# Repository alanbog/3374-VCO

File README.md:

# 3374-VCO

This repository contains a circuit designed to be a clone of the CEM 3374 VCO IC used in analog synthesizers from the early 1980s such as:

* Fender Chroma Polaris
* Oberheim Matrix 12
* Oberheim Xpander
* Akai VX600.

It is designed to operate with 12V for Vcc and -5V or -6V for Vee, which is what all of the synthesizers listed above use for supply voltages. The circuit contains two oscillator channels with triangle and sawtooth wave outputs. Triangle wave outputs have an amplitude of 1/3 Vcc, and sawtooth wave outputs have an amplitude of 2/3 Vcc. Synthesizers using the CEM 3374 that generate square/pulse waves do so with external comparator circuits. 

Channel A sync is implemented. Channel B sync is not implemented, but this feature was rarely used on the CEM 3374 (None of the synthesizers listed above use it). 

A thermistor circuit is used to provede a temperature compensated reference voltage. Typically, this voltage is used as a reference for the DAC that outputs the voltage that controls the frequency of the oscillators.

This was tested on a Chroma Polaris. It should work in all of the other synthesizers listed above, but it hasn't been tested. 

For Rev 1, the oscillator circuit was updated to fix an issue with Oberheim Synthesizers being out of tune at lower notes (although this fix hasn't yet been tested on an Oberheim synthesizer).

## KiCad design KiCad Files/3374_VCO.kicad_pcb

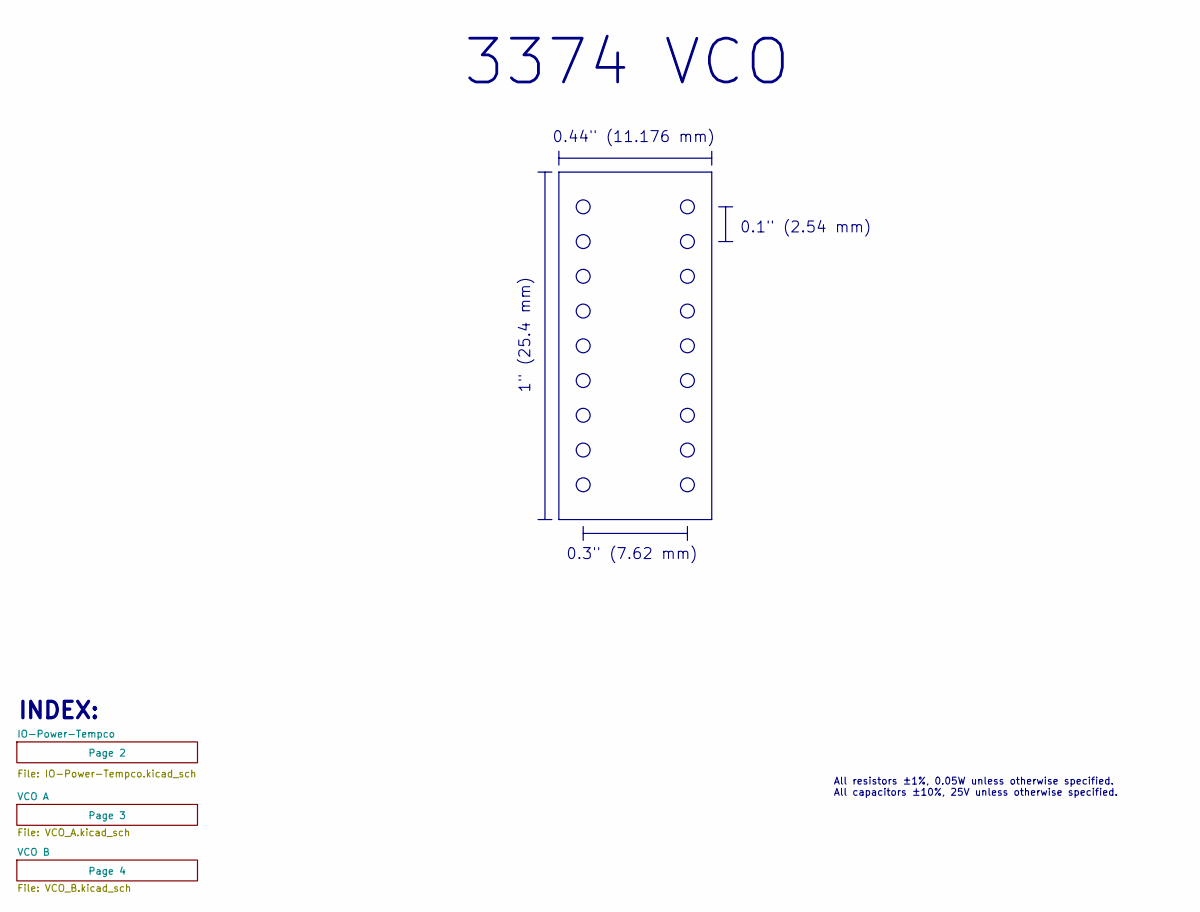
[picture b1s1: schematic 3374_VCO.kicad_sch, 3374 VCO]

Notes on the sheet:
INDEX:
0.3" (7.62 mm)
All resistors ±1%, 0.05W unless otherwise specified. All capacitors ±10%, 25V unless otherwise specified.
0.44" (11.176 mm)
3374 VCO
1" (25.4 mm)
0.1" (2.54 mm)

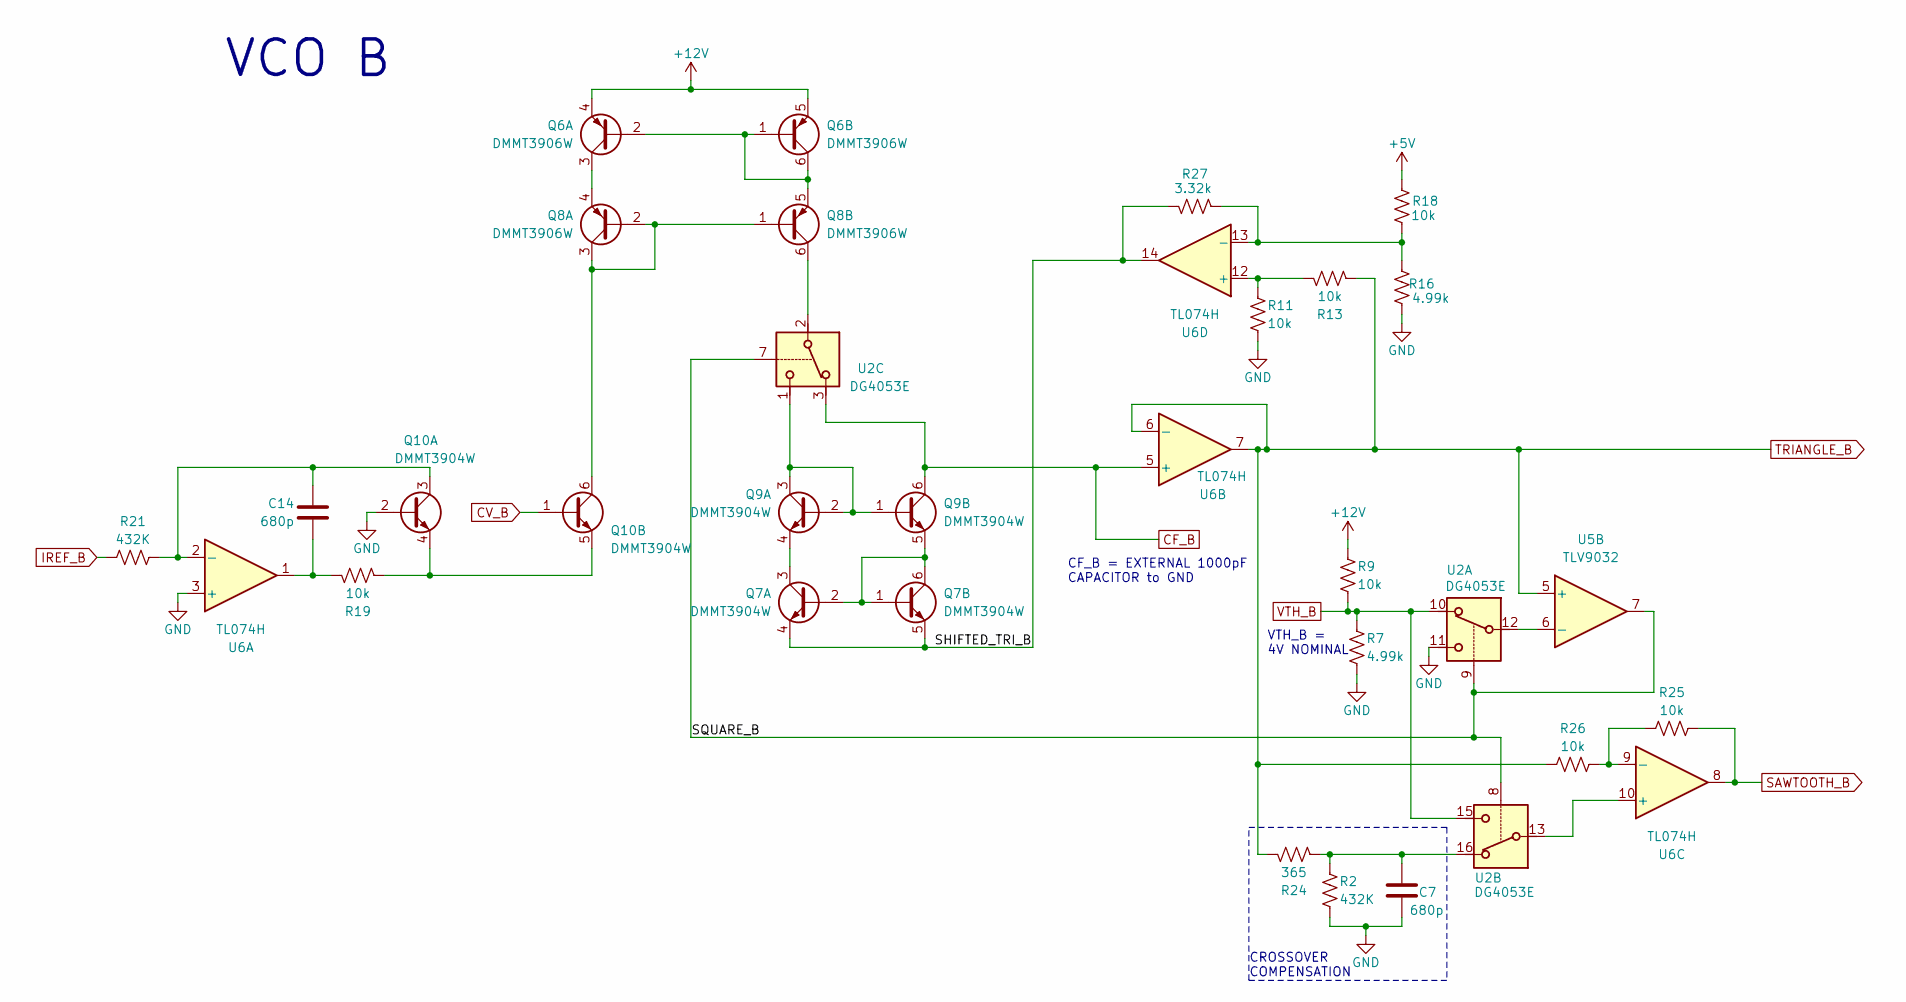
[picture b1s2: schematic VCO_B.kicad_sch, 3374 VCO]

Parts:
C7, C14: 680p; C_0201_0603Metric; Rating 25V; Tolerance 10%; Mfg PN GRM033R71E681KA01D
Q6, Q8: DMMT3906W; SOT-363_SC-70-6; Mfg PN DMMT3906W-7-F
Q7, Q9, Q10: DMMT3904W; SOT-363_SC-70-6; Mfg PN DMMT3904W-7-F
R2, R21: 432K; R_0201_0603Metric; Rating 0.05W; Tolerance 1%; Mfg PN WR02X4323FAL
R7, R16: 4.99k; R_0201_0603Metric; Rating 0.05W; Tolerance 1%; Mfg PN 0201WMF4991TEE
R9, R11, R13, R18, R19, R25, R26: 10k; R_0201_0603Metric; Rating 0.05W; Tolerance 1%; Mfg PN 0201WMF1002TEE
R24: 365; R_0201_0603Metric; Rating 0.05W; Tolerance 1%; Mfg PN 0201WMF3650TEE
R27: 3.32k; R_0201_0603Metric; Rating 0.05W; Tolerance 1%; Mfg PN 0201WMF3321TEE
U2: DG4053E; QFN_EEN-T1-GE4_VIS; Mfg PN DG4053EEN-T1-GE4
U5: TLV9032; WSON-8-1EP_2x2mm_P0.5mm_EP0.9x1.6mm; Mfg PN TLV9032DSGR
U6: TL074H; SOT23_DYY_TEX-L; Mfg PN TL074HIDYYR

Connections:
+5V: R18.2; also elsewhere on the board
+12V: Q6.4 (E1), Q6.5 (E2), R9.1; also elsewhere on the board
/VCO B/SHIFTED_TRI_B: Q7.4 (E1), Q7.5 (E2), R27.1, U6.14
/VCO B/SQUARE_B: U2.7, U2.8, U2.9, U5.7
CF_B: Q9.6 (C2), U2.3, U6.5 (+); also elsewhere on the board
CV_B: Q10.1 (B2); also elsewhere on the board
GND: C7.2, Q10.2 (B1), R2.2, R7.2, R11.2, R16.2, U2.11, U6.3 (+); also elsewhere on the board
IREF_B: R21.1; also elsewhere on the board
unnamed: C7.1, R2.1, R24.2, U2.16
unnamed: C14.2, R19.1, U6.1
unnamed: Q6.1 (B2), Q6.2 (B1), Q6.6 (C2), Q8.5 (E2)
unnamed: Q6.3 (C1), Q8.4 (E1)
unnamed: Q7.1 (B2), Q7.2 (B1), Q7.6 (C2), Q9.5 (E2)
unnamed: Q7.3 (C1), Q9.4 (E1)
unnamed: Q8.6 (C2), U2.2
unnamed: Q9.1 (B2), Q9.2 (B1), Q9.3 (C1), U2.1
unnamed: C14.1, Q10.3 (C1), R21.2, U6.2 (-)
unnamed: Q10.4 (E1), Q10.5 (E2), R19.2
unnamed: Q8.1 (B2), Q8.2 (B1), Q8.3 (C1), Q10.6 (C2)
unnamed: U2.12, U5.6 (-)
unnamed: U2.13, U6.10 (+)
unnamed: R25.1, R26.2, U6.9 (-)
unnamed: R11.1, R13.1, U6.12 (+)
unnamed: R16.1, R18.1, R27.2, U6.13 (-)
SAWTOOTH_B: R25.2, U6.8; also elsewhere on the board
TRIANGLE_B: R13.2, R24.1, R26.1, U5.5 (+), U6.6 (-), U6.7; also elsewhere on the board
VTH_B: R7.1, R9.2, U2.10, U2.15; also elsewhere on the board

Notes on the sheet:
CROSSOVER COMPENSATION
VCO B
VTH_B = 4V NOMINAL
CF_B = EXTERNAL 1000pF CAPACITOR to GND

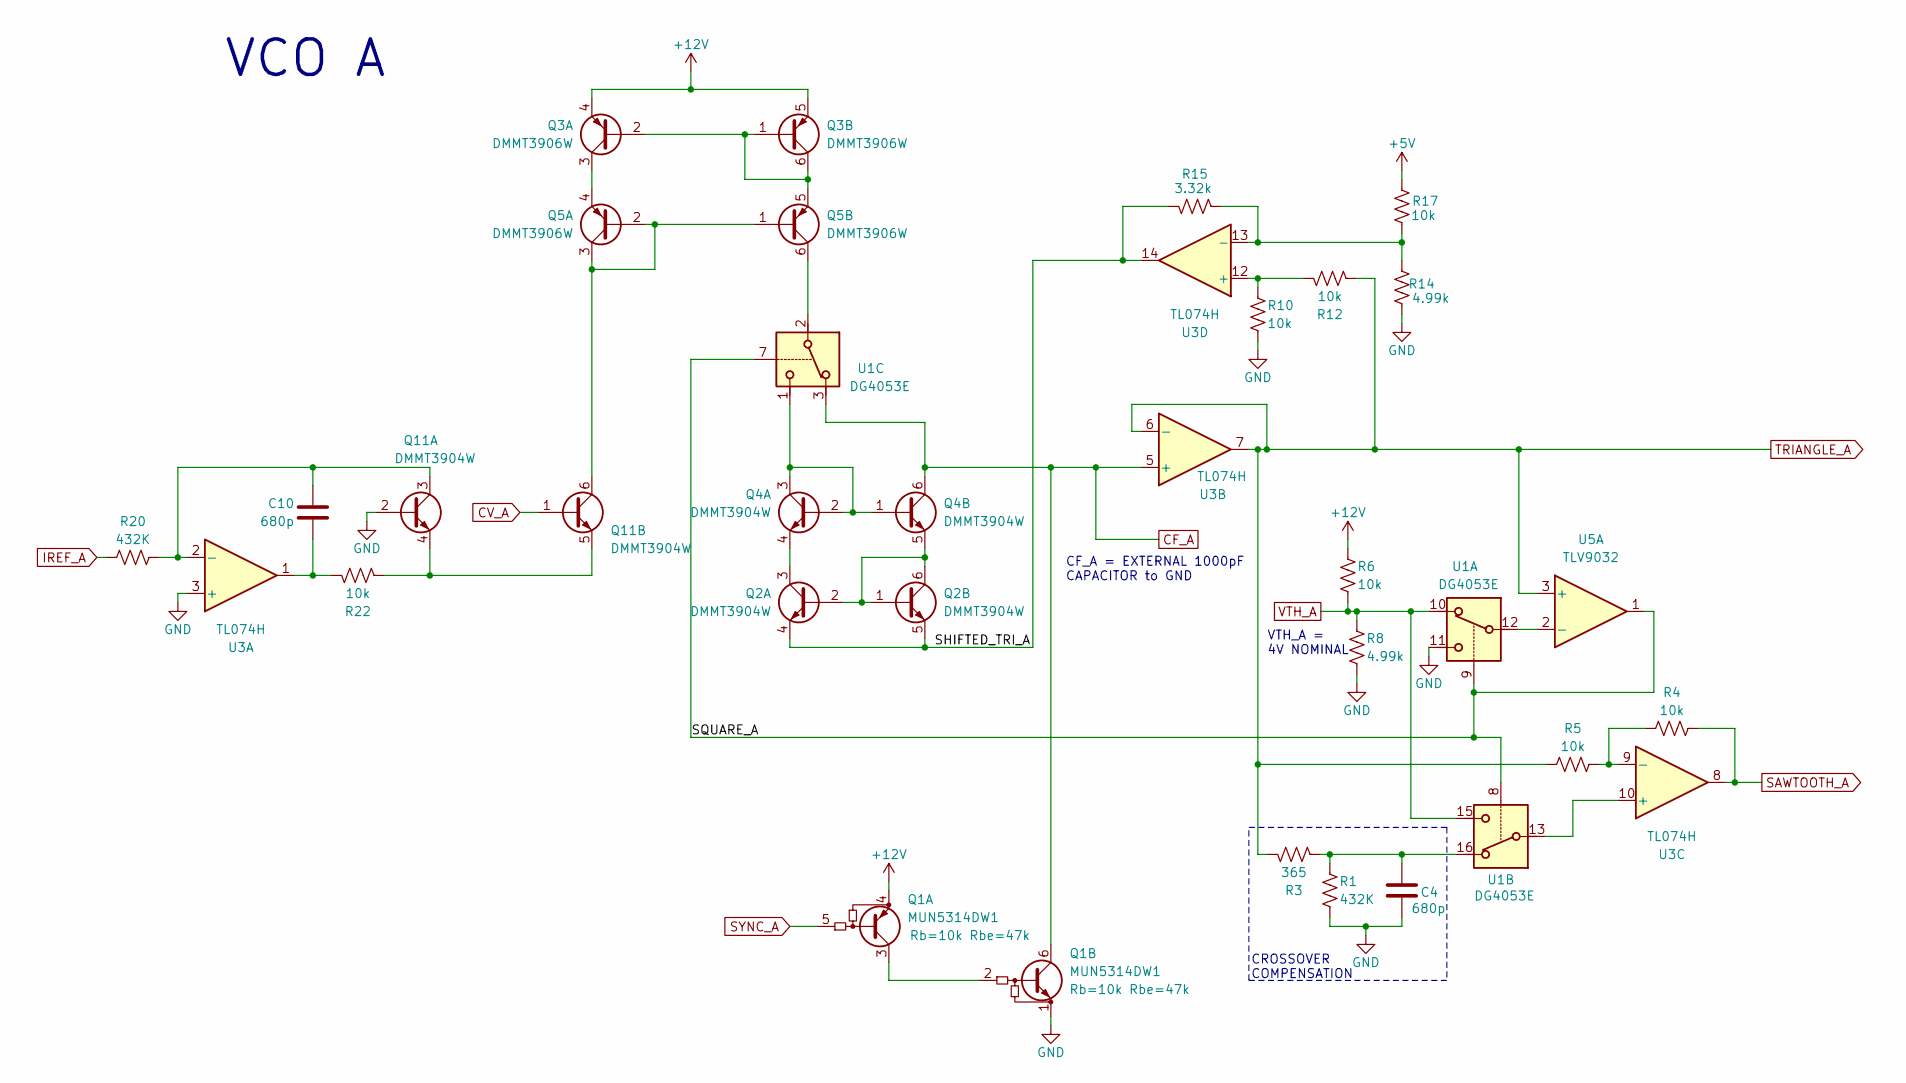
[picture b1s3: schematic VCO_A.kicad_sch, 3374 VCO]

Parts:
C4, C10: 680p; C_0201_0603Metric; Rating 25V; Tolerance 10%; Mfg PN GRM033R71E681KA01D
Q1: MUN5314DW1; SOT-363_SC-70-6; Mfg PN LMUN5314DW1T1G
Q2, Q4, Q11: DMMT3904W; SOT-363_SC-70-6; Mfg PN DMMT3904W-7-F
Q3, Q5: DMMT3906W; SOT-363_SC-70-6; Mfg PN DMMT3906W-7-F
R1, R20: 432K; R_0201_0603Metric; Rating 0.05W; Tolerance 1%; Mfg PN WR02X4323FAL
R3: 365; R_0201_0603Metric; Rating 0.05W; Tolerance 1%; Mfg PN 0201WMF3650TEE
R4, R5, R6, R10, R12, R17, R22: 10k; R_0201_0603Metric; Rating 0.05W; Tolerance 1%; Mfg PN 0201WMF1002TEE
R8, R14: 4.99k; R_0201_0603Metric; Rating 0.05W; Tolerance 1%; Mfg PN 0201WMF4991TEE
R15: 3.32k; R_0201_0603Metric; Rating 0.05W; Tolerance 1%; Mfg PN 0201WMF3321TEE
U1: DG4053E; QFN_EEN-T1-GE4_VIS; Mfg PN DG4053EEN-T1-GE4
U3: TL074H; SOT23_DYY_TEX-L; Mfg PN TL074HIDYYR
U5: TLV9032; WSON-8-1EP_2x2mm_P0.5mm_EP0.9x1.6mm; Mfg PN TLV9032DSGR

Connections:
+5V: R17.2; also elsewhere on the board
+12V: Q1.4 (E1), Q3.4 (E1), Q3.5 (E2), R6.1; also elsewhere on the board
/VCO A/SHIFTED_TRI_A: Q2.4 (E1), Q2.5 (E2), R15.1, U3.14
/VCO A/SQUARE_A: U1.7, U1.8, U1.9, U5.1
CF_A: Q1.6 (C2), Q4.6 (C2), U1.3, U3.5 (+); also elsewhere on the board
CV_A: Q11.1 (B2); also elsewhere on the board
GND: C4.2, Q1.1 (E2), Q11.2 (B1), R1.2, R8.2, R10.2, R14.2, U1.11, U3.3 (+); also elsewhere on the board
IREF_A: R20.1; also elsewhere on the board
unnamed: C4.1, R1.1, R3.2, U1.16
unnamed: C10.2, R22.1, U3.1
unnamed: Q1.2 (B2), Q1.3 (C1)
unnamed: Q2.1 (B2), Q2.2 (B1), Q2.6 (C2), Q4.5 (E2)
unnamed: Q2.3 (C1), Q4.4 (E1)
unnamed: Q3.1 (B2), Q3.2 (B1), Q3.6 (C2), Q5.5 (E2)
unnamed: Q3.3 (C1), Q5.4 (E1)
unnamed: Q4.1 (B2), Q4.2 (B1), Q4.3 (C1), U1.1
unnamed: Q5.6 (C2), U1.2
unnamed: C10.1, Q11.3 (C1), R20.2, U3.2 (-)
unnamed: Q11.4 (E1), Q11.5 (E2), R22.2
unnamed: Q5.1 (B2), Q5.2 (B1), Q5.3 (C1), Q11.6 (C2)
unnamed: U1.13, U3.10 (+)
unnamed: R4.1, R5.2, U3.9 (-)
unnamed: R10.1, R12.1, U3.12 (+)
unnamed: R14.1, R15.2, R17.1, U3.13 (-)
unnamed: U1.12, U5.2 (-)
SAWTOOTH_A: R4.2, U3.8; also elsewhere on the board
SYNC_A: Q1.5 (B1); also elsewhere on the board
TRIANGLE_A: R3.1, R5.1, R12.2, U3.6 (-), U3.7, U5.3 (+); also elsewhere on the board
VTH_A: R6.2, R8.1, U1.10, U1.15; also elsewhere on the board

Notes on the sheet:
CF_A = EXTERNAL 1000pF CAPACITOR to GND
VTH_A = 4V NOMINAL
VCO A
CROSSOVER COMPENSATION

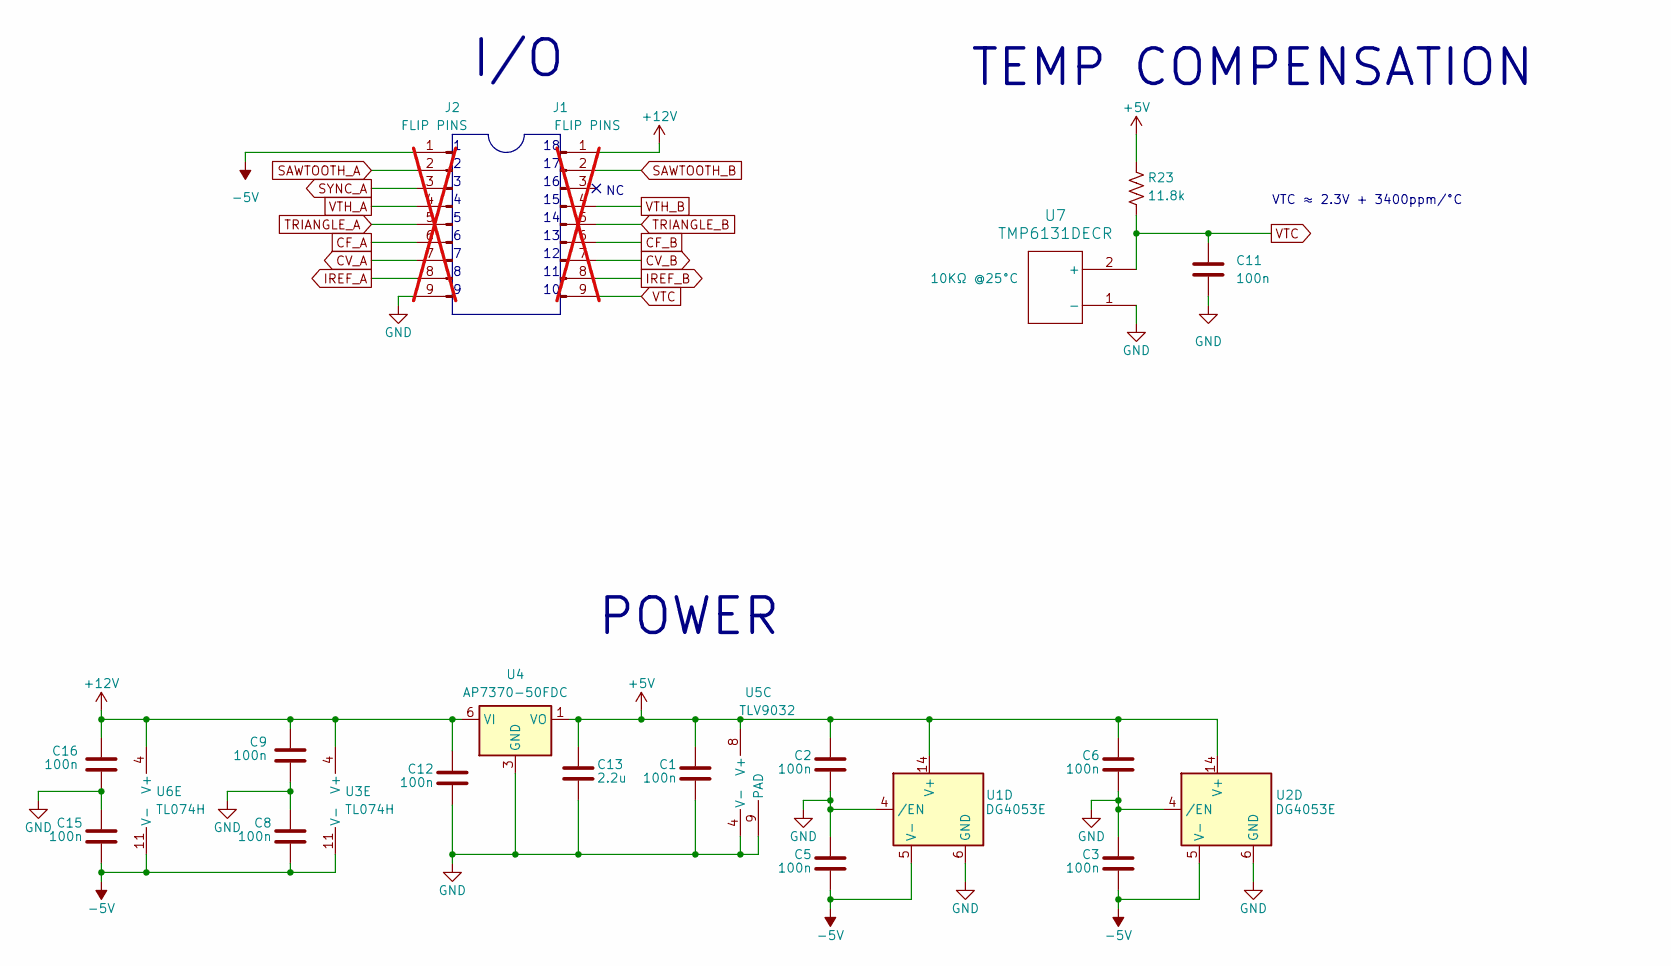
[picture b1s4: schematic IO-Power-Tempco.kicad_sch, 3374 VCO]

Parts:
C1, C2, C3, C5, C6, C8, C9, C11, C12, C15, C16: 100n; C_0201_0603Metric; Rating 25V; Tolerance 10%; Mfg PN 0201X104K250CT
C13: 2.2u; C_0402_1005Metric; Rating 25V; Tolerance 10%; Mfg PN GRM155R61E225KE11D
J1, J2: FLIP PINS; FLIP-PINS-FLOAT-09; Mfg PN FLIP-PINS-09; not fitted
R23: 11.8k; R_0201_0603Metric; Rating 0.05W; Tolerance 1%; Mfg PN AC0201FR-0711K8L
U1, U2: DG4053E; QFN_EEN-T1-GE4_VIS; Mfg PN DG4053EEN-T1-GE4
U3, U6: TL074H; SOT23_DYY_TEX-L; Mfg PN TL074HIDYYR
U4: AP7370-50FDC; DFN-6-1EP_2x2mm_P0.65mm_EP1.01x1.7mm; Mfg PN AP7370-50FDC-7
U5: TLV9032; WSON-8-1EP_2x2mm_P0.5mm_EP0.9x1.6mm; Mfg PN TLV9032DSGR
U7: TMP6131DECR; X1SON2_1XP65_TEX-L; Mfg PN TMP6131DECR

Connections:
+5V: C1.1, C2.1, C6.1, C13.1, R23.1, U1.14 (V+), U2.14 (V+), U4.1 (VO), U5.8 (V+); also elsewhere on the board
+12V: C9.1, C12.1, C16.1, J1.1, U3.4 (V+), U4.6 (VI), U6.4 (V+); also elsewhere on the board
-5V: C3.2, C5.2, C8.2, C15.2, J2.1, U1.5 (V-), U2.5 (V-), U3.11 (V-), U6.11 (V-)
CF_A: J2.6; also elsewhere on the board
CF_B: J1.6; also elsewhere on the board
CV_A: J2.7; also elsewhere on the board
CV_B: J1.7; also elsewhere on the board
GND: C1.2, C2.2, C3.1, C5.1, C6.2, C8.1, C9.2, C11.2, C12.2, C13.2, C15.1, C16.2, J2.9, U1.4 (/EN), U1.6 (GND), U2.4 (/EN), U2.6 (GND), U4.3 (GND), U4.7 (GND), U5.4 (V-), U5.9 (PAD), U7.1 (-); also elsewhere on the board
IREF_A: J2.8; also elsewhere on the board
IREF_B: J1.8; also elsewhere on the board
SAWTOOTH_A: J2.2; also elsewhere on the board
SAWTOOTH_B: J1.2; also elsewhere on the board
SYNC_A: J2.3; also elsewhere on the board
TRIANGLE_A: J2.5; also elsewhere on the board
TRIANGLE_B: J1.5; also elsewhere on the board
VTC: C11.1, J1.9, R23.2, U7.2 (+)
VTH_A: J2.4; also elsewhere on the board
VTH_B: J1.4; also elsewhere on the board

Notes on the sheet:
I/O
VTC ≈ 2.3V + 3400ppm/°C
TEMP COMPENSATION
POWER

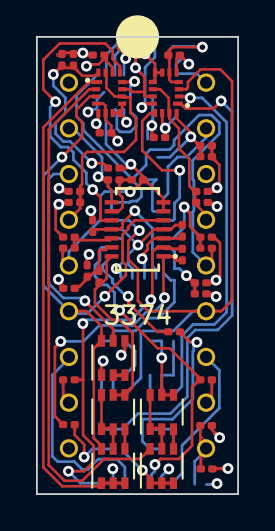
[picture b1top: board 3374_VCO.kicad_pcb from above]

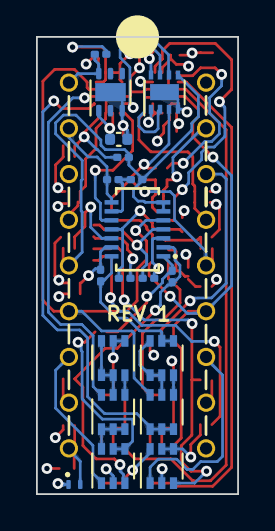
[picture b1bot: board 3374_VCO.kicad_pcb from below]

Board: 4 copper layers, 11.2 x 25.4 mm, 63 parts (21 on the bottom side), 55 nets.

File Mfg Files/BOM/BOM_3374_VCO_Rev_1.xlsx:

3374 VCO Rev 1 BOM (12-Dec-2024)
# | Reference | Qty | Value | DNP | Description | Mfg | Mfg PN | Distributor | Distributor PN | Package | Type | Substitute part okay?
1 | C1,C2,C3,C5,C6,C8,C9,C11,C12,C15,C16 | 11 | 100n |  | Capacitor, 100nF, 10%, 25V, X5R | Walsin | 0201X104K250CT | LCSC | C880779 | 201 | SMD | Yes
2 | C4,C7,C10,C14 | 4 | 680p |  | Capacitor, 680pF, 10%, 25V, X7R | Murata | GRM033R71E681KA01D | LCSC | C161490 | 201 | SMD | Yes
3 | C13 | 1 | 2.2u |  | Capacitor, 2.2uF, 10%, 25V, X5R | Murata | GRM155R61E225KE11D | LCSC | C385032 | 402 | SMD | Yes
4 | J1,J2 | 2 | FLIP PINS | DNP | Flip Pins, 9-pin | Fliptronics | FLIP-PINS-09 |  |  | FLIP-PINS-09 | DNP
5 | Q1 | 1 | MUN5314DW1 |  | Transistor, Dual Complementary Prebiased, Rb=10k, Rbe=47k | LRC | LMUN5314DW1T1G | LCSC | C417318 | SC-88 | SMD | No
6 | Q2,Q4,Q7,Q9,Q10,Q11 | 6 | DMMT3904W |  | Transistor, Dual Matched NPN | Diodes Inc | DMMT3904W-7-F | LCSC | C155305 | SC-88 | SMD | No
7 | Q3,Q5,Q6,Q8 | 4 | DMMT3906W |  | Transistor, Dual Matched PNP | Diodes Inc | DMMT3906W-7-F | LCSC | C151567 | SC-88 | SMD | No
8 | R1,R2,R20,R21 | 4 | 432K |  | Resistor, 432k Ohm, 1%, 0.05W | Walsin | WR02X4323FAL | LCSC | C367623 | 201 | SMD | Yes
9 | R3,R24 | 2 | 365 |  | Resistor, 365 Ohm, 1%, 0.05W | Uniroyal | 0201WMF3650TEE | LCSC | C423558 | 201 | SMD | Yes
10 | R4,R5,R6,R9,R10,R11,R12,R13,R17,R18,R19,R22,R25,R26 | 14 | 10k |  | Resistor, 10k Ohm, 1%, 0.05W | Uniroyal | 0201WMF1002TEE | LCSC | C473048 | 201 | SMD | Yes
11 | R7,R8,R14,R16 | 4 | 4.99k |  | Resistor, 4.99k Ohm, 1%, 0.05W | Uniroyal | 0201WMF4991TEE | LCSC | C473528 | 201 | SMD | Yes
12 | R15,R27 | 2 | 3.32k |  | Resistor, 3.32k Ohm, 1%, 0.05W | Uniroyal | 0201WMF3321TEE | LCSC | C474121 | 201 | SMD | Yes
13 | R23 | 1 | 11.8k |  | Resistor, 11.8k Ohm, 1%, 0.05W | Yageo | AC0201FR-0711K8L | LCSC | C910595 | 201 | SMD | Yes
14 | U1,U2 | 2 | DG4053E |  | Triple SPDT CMOS Analog Switch | Vishay | DG4053EEN-T1-GE4 | Mouser | 78-DG4053EEN-T1-GE4 | 16-miniQFN | SMD | No
15 | U3,U6 | 2 | TL074H |  | IC, Quad Op Amp | Texas Instruments | TL074HIDYYR | Mouser | 595-TL074HIDYYR | 14-SOT-23-THIN | SMD | No
16 | U4 | 1 | AP7370-50FDC |  | IC, LDO, 5V | Diodes Inc | AP7370-50FDC-7 | Mouser | 621-AP7370-50FDC-7 | 6-UDFN | SMD | No
17 | U5 | 1 | TLV9032 |  | IC, Dual Comparator | Texas Instruments | TLV9032DSGR | Mouser | 595-TLV9032DSGR | 8-WSON | SMD | No
18 | U7 | 1 | TMP6131DECR |  | IC, 10k PTC Thermistor | Texas Instruments | TMP6131DECR | LCSC | C2870682 | 2-X1SON | SMD | No
 | Notes:
 | DNP = Do Not Populate.
 | The distributor indicated in the BOM is a suggestion. Any authorized distibutor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

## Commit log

2024-03-11 Uploaded files
2024-03-11 Create license.txt
    Added license
2024-03-14 Added test report and photo
2025-01-19 Updated to Rev 1
